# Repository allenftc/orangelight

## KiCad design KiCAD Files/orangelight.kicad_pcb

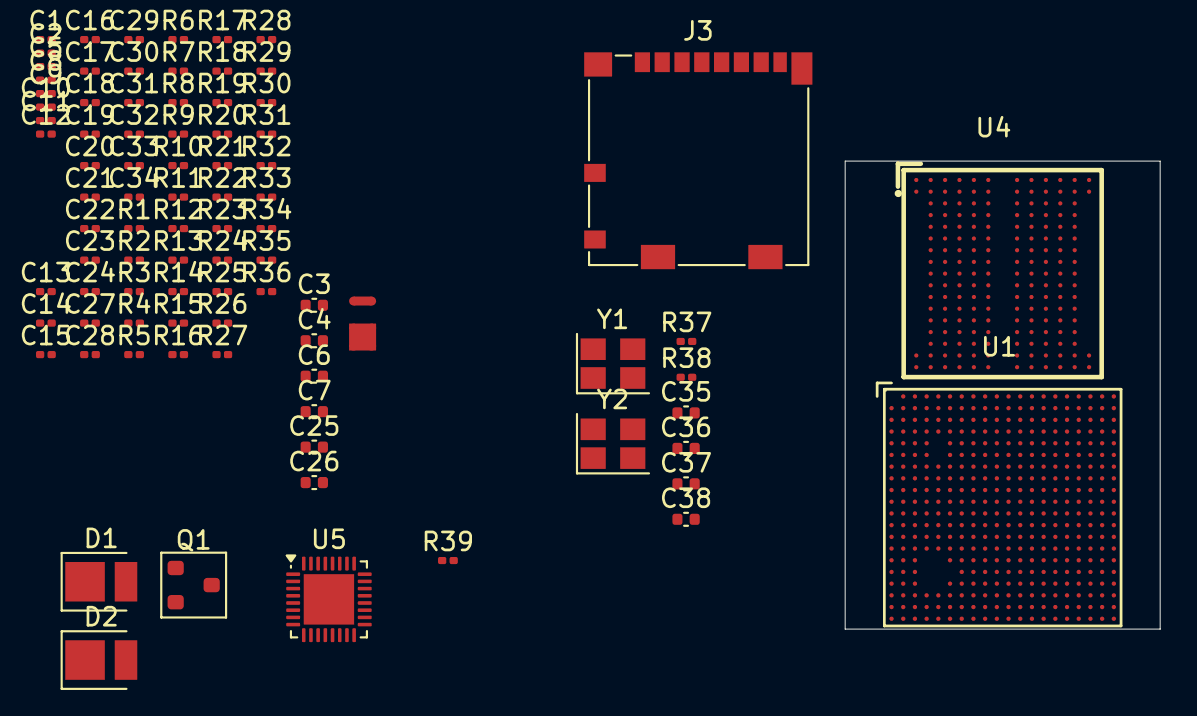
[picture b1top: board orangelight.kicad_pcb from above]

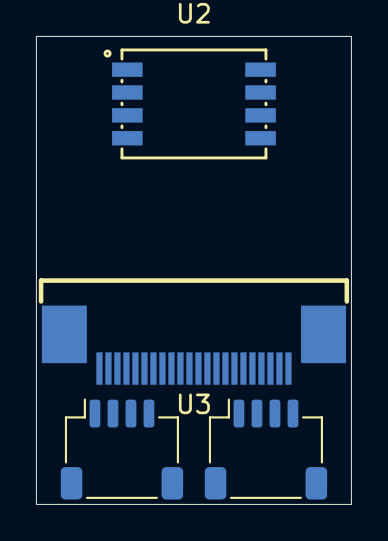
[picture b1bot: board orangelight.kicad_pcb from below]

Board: 2 copper layers, 17.5 x 26.0 mm, 92 parts (4 on the bottom side), 79 nets, no tracks yet.

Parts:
C1, C2, C5, C8, C9, C10, C11, C12, C13, C14, C15, C16, C17, C18, C19, C20, C21, C22, C23, C24, C27, C28, C29, C30, C31, C32, C33, C34: 100nF; C_0201_0603Metric
C3, C6, C25: 22uF; C_0402_1005Metric
C4, C7, C26: 4.7uF; C_0402_1005Metric
C35, C36, C37, C38: 15pF; C_0402_1005Metric
D1, D2: LED; LED_PLCC_2835
J1, J2: REV_JST_SMD; JST_SH_SM04B-SRSS-TB_1x04-1MP_P1.00mm_Horizontal
J3: Micro_SD_Card_Det2; microSD_HC_Molex_104031-0811
NT1: NetTie_2; NetTie-2_SMD_Pad0.5mm
NT2: NetTie_4; NetTie-4_SMD_Pad0.5mm
Q1: 2N7002; SOT-23
R1, R2, R36: 240R; R_0201_0603Metric
R3, R4, R5, R6, R7, R8, R9, R10, R11, R12, R13, R14, R15, R16, R17, R18, R19, R20, R21, R22, R23, R24, R25, R26, R27, R28, R29, R30, R31, R32, R33, R34, R35: 120R; R_0201_0603Metric
R37, R38: 1M; R_0201_0603Metric
R39: 200R; R_0201_0603Metric
U1: K230_Rewired; BGA-390_L13.0-W13.0-P0.65-TL_C9900054646
U2: ZDSD04GLGEAG; LGA-8_L8.0-W6.0-P1.27-TL-1
U3: HC-FPC-0_5-22P-CXH20; FPC-SMD_22P-P0.50_HC-FPC-0.5-22P-CXH20
U4: K4E8E324ED-EGCG; BGA-178_L11.5W11.0-P0.65-TL
U5: RT9992ZQW; Texas_RSN_WQFN-32-1EP_4x4mm_P0.4mm_EP2.8x2.8mm
Y1, Y2: 32.768KHz; Crystal_SMD_Abracon_ABM8AIG-4Pin_3.2x2.5mm

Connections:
+3V3: J1.3 (3.3V), J2.3 (3.3V), J3.4 (VDD), Q1.3 (D), U2.8 (VDD)
/RAM/DDR.CA0: R13.2, R14.1, U1.K20 (DDR_CA0_NC), U4.R2 (CA0)
/RAM/DDR.CA1: R15.2, R16.1, U1.L20 (DDR_CA1_NC), U4.P2 (CA1)
/RAM/DDR.CA2: R17.2, R18.1, U1.M20 (DDR_CA2_NA), U4.N2 (CA2)
/RAM/DDR.CA3: R19.2, R20.1, U1.L17 (DDR_CA3_NC), U4.N3 (CA3)
/RAM/DDR.CA4: R21.2, R22.1, U1.M19 (DDR_CA4_CAA0), U4.M3 (CA4)
/RAM/DDR.CA5: R23.2, R24.1, U1.L16 (DDR_CA5_CAA1), U4.F3 (CA5)
/RAM/DDR.CA6: R25.2, R26.1, U1.N19 (DDR_CA6_CAA2), U4.E3 (CA6)
/RAM/DDR.CA7: R27.2, R28.1, U1.N20 (DDR_CA7_CAA3), U4.E2 (CA7)
/RAM/DDR.CA8: R29.2, R30.1, U1.M18 (DDR_CA8_CAA4), U4.D2 (CA8)
/RAM/DDR.CA9: R31.2, R32.1, U1.P19 (DDR_CA9_CAA5), U4.C2 (CA9)
/RAM/DDR.CS: R3.2, R4.1, U4.L3 (CS_N)
/RAM/DDR.DM0: U1.D18 (DDR_DM0_DMIB0), U4.L8 (DM0)
/RAM/DDR.DM1: U1.P17 (DDR_DM1_DMIA1), U4.G8 (DM1)
/RAM/DDR.DM2: U1.C15 (DDR_DM2_DMIB1), U4.P8 (DM2)
/RAM/DDR.DM3: U1.V17 (DDR_DM3_DMIA0), U4.D8 (DM3)
/RAM/DDR.DQS_N0: U1.A18 (DDR_DQS0N_DQSB0N), U4.L11 (DQS0_c)
/RAM/DDR.DQS_N1: U1.V19 (DDR_DQS1N_DQSA1N), U4.G11 (DQS1_c)
/RAM/DDR.DQS_N2: U1.A15 (DDR_DQS2N_DQSB1N), U4.P11 (DQS2_c)
/RAM/DDR.DQS_N3: U1.Y17 (DDR_DQS3N_DQSA0N), U4.D11 (DQS3_c)
/RAM/DDR.DQS_P0: U1.B18 (DDR_DQS0P_DQSB0P), U4.L10 (DQS0_t)
/RAM/DDR.DQS_P1: U1.V20 (DDR_DQS1P_DQSA1P), U4.G10 (DQS1_t)
/RAM/DDR.DQS_P2: U1.B15 (DDR_DQS2P_DQSB1P), U4.P10 (DQS2_t)
/RAM/DDR.DQS_P3: U1.W17 (DDR_DQS3P_DQSA0P), U4.D10 (DQS3_t)
/RAM/DDR.ODT: R9.2, R10.1, U4.J8 (ODT(1))
/RAM/DDR.VREF_CA: C1.1, R33.2, R34.1, U4.H4 (VRef(CA))
/RAM/DDR.VREF_DQ: C2.1, R35.2, R36.1, U4.J11 (VRef(DQ))
/RAM/DDR_CK+: R7.2, R8.1, U4.J3 (CK_P)
/RAM/DDR_CK-: R5.2, R6.1, U4.J2 (CK_N)
/RAM/DDR_CKE: R11.2, R12.1, U4.K3 (CKE)
DDR_VDD1: C25.1, C26.1, C29.1, C30.1, C31.1, C32.1, C33.1, C34.1, NT1.2, U4.A3 (VDD1), U4.A4 (VDD1), U4.A5 (VDD1), U4.A6 (VDD1), U4.A10 (VDD1), U4.U3 (VDD1), U4.U4 (VDD1), U4.U5 (VDD1), U4.U6 (VDD1), U4.U10 (VDD1)
DDR_VDD2: NT2.2, U4.A8 (VDD2), U4.A9 (VDD2), U4.D4 (VDD2), U4.D5 (VDD2), U4.D6 (VDD2), U4.G5 (VDD2), U4.H5 (VDD2), U4.H6 (VDD2), U4.H12 (VDD2), U4.J5 (VDD2), U4.J6 (VDD2), U4.K5 (VDD2), U4.K6 (VDD2), U4.K12 (VDD2), U4.L5 (VDD2), U4.P4 (VDD2), U4.P5 (VDD2), U4.P6 (VDD2), U4.U8 (VDD2), U4.U9 (VDD2)
DDR_VDDCA: NT2.3, U4.F2 (VDDCA), U4.G2 (VDDCA), U4.H3 (VDDCA), U4.L2 (VDDCA), U4.M2 (VDDCA)
DDR_VDDQ: C3.1, C4.1, C5.1, C6.1, C7.1, C8.1, C9.1, C10.1, C11.1, C12.1, C13.1, C14.1, C15.1, C16.1, C17.1, C18.1, C19.1, C20.1, C21.1, C22.1, C23.1, C24.1, C27.1, C28.1, NT2.4, R3.1, R5.1, R7.1, R9.1, R11.1, R13.1, R15.1, R17.1, R19.1, R21.1, R23.1, R25.1, R27.1, R29.1, R31.1, R33.1, R35.1, U4.A11 (VDDQ), U4.C12 (VDDQ), U4.E8 (VDDQ), U4.E12 (VDDQ), U4.G12 (VDDQ), U4.H8 (VDDQ), U4.H9 (VDDQ), U4.H11 (VDDQ), U4.J9 (VDDQ), U4.J10 (VDDQ), U4.K8 (VDDQ), U4.K11 (VDDQ), U4.L12 (VDDQ), U4.N8 (VDDQ), U4.N12 (VDDQ), U4.R12 (VDDQ), U4.U11 (VDDQ)
GND: C1.2, C2.2, C3.2, C4.2, C5.2, C6.2, C7.2, C8.2, C9.2, C10.2, C11.2, C12.2, C13.2, C14.2, C15.2, C16.2, C17.2, C18.2, C19.2, C20.2, C21.2, C22.2, C23.2, C24.2, C25.2, C26.2, C27.2, C28.2, C29.2, C30.2, C31.2, C32.2, C33.2, C34.2, C35.2, C36.2, C37.2, C38.2, D1.1 (K), D2.1 (K), J1.4 (GND), J2.4 (GND), J3.6 (VSS), J3.11 (SHIELD), R1.2, R2.2, R4.2, R6.2, R8.2, R10.2, R12.2, R14.2, R16.2, R18.2, R20.2, R22.2, R24.2, R26.2, R28.2, R30.2, R32.2, R34.2, R36.2, R39.1, U2.4 (GND), U4.B2 (VSS), U4.B5 (VSS), U4.B6 (VSSQ), U4.B12 (VSSQ), U4.C3 (VSSCA), U4.C5 (VSS), U4.C6 (VSSQ), U4.D3 (VSSCA), U4.D12 (VSSQ), U4.E4 (VSS), U4.E5 (VSS), U4.E6 (VSSQ), U4.F4 (VSSCA), U4.F5 (VSS), U4.F6 (VSSQ), U4.F12 (VSSQ), U4.G3 (VSSCA), U4.G4 (VSSCA), U4.G6 (VSSQ), U4.G9 (VSSQ), U4.H2 (VSS), U4.H10 (VSSQ), U4.J4 (VSSCA), U4.J12 (VSS), U4.K2 (VSS), U4.K10 (VSSQ), U4.L6 (VSS), U4.L9 (VSSQ), U4.M4 (VSSCA), U4.M5 (VSSCA), U4.M6 (VSSQ), U4.M12 (VSSQ), U4.N4 (VSS), U4.N5 (VSS), U4.N6 (VSSQ), U4.P3 (VSSCA), U4.P12 (VSSQ), U4.R4 (VSS), U4.R5 (VSS), U4.R6 (VSSQ), U4.T2 (VSS), U4.T3 (VSS), U4.T4 (VSS), U4.T5 (VSS), U4.T6 (VSSQ), U4.T12 (VSSQ), Y1.2, Y1.4, Y2.2, Y2.4
unnamed: D1.2 (A), D2.2 (A), Q1.2 (S)
unnamed: J3.9 (DET_B), J3.10 (DET_A)
unnamed: C35.1, R37.2, Y1.3
unnamed: C36.1, R37.1, Y1.1
unnamed: C38.1, R38.2, Y2.3
unnamed: C37.1, R38.1, Y2.1
unnamed: U1.C17 (DDR_DQ0_DQB4), U4.P9 (DQ0)
unnamed: U1.D16 (DDR_DQ1_DQB1), U4.N9 (DQ1)
unnamed: U1.D17 (DDR_DQ2_DQB0), U4.N10 (DQ2)
unnamed: U1.C18 (DDR_DQ3_DQB5), U4.N11 (DQ3)
unnamed: U1.E18 (DDR_DQ4_DQB2), U4.M8 (DQ4)
unnamed: U1.E17 (DDR_DQ5_DQB3), U4.M9 (DQ5)
unnamed: U1.B19 (DDR_DQ6_DQB7), U4.M10 (DQ6)
unnamed: U1.C19 (DDR_DQ7_DQB6), U4.M11 (DQ7)
unnamed: U1.R18 (DDR_DQ8_DQA10), U4.F11 (DQ8)
unnamed: U1.P16 (DDR_DQ9_DQA14), U4.F10 (DQ9)
unnamed: U1.R17 (DDR_DQ10_DQA8), U4.F9 (DQ10)
unnamed: U1.W19 (DDR_DQ11_DQA12), U4.F8 (DQ11)
unnamed: U1.T18 (DDR_DQ12_DQA9), U4.E11 (DQ12)
unnamed: U1.U20 (DDR_DQ13_DQA11), U4.E10 (DQ13)
unnamed: U1.U18 (DDR_DQ14_DQA13), U4.E9 (DQ14)
unnamed: U1.T17 (DDR_DQ15_DQA15), U4.D9 (DQ15)
unnamed: U1.C14 (DDR_DQ16_DQB11), U4.T8 (DQ16)
unnamed: U1.B14 (DDR_DQ17_DQB10), U4.T9 (DQ17)
unnamed: U1.C16 (DDR_DQ18_DQB13), U4.T10 (DQ18)
unnamed: U1.A17 (DDR_DQ19_DQB14), U4.T11 (DQ19)
unnamed: U1.D14 (DDR_DQ20_DQB8), U4.R8 (DQ20)
unnamed: U1.A14 (DDR_DQ21_DQB9), U4.R9 (DQ21)
unnamed: U1.B17 (DDR_DQ22_DQB12), U4.R10 (DQ22)
unnamed: U1.B16 (DDR_DQ23_DQB15), U4.R11 (DQ23)
unnamed: U1.W18 (DDR_DQ24_DQA4), U4.C11 (DQ24)
unnamed: U1.V18 (DDR_DQ25_DQA5), U4.C10 (DQ25)
unnamed: U1.V16 (DDR_DQ26_DQA2), U4.C9 (DQ26)
unnamed: U1.Y16 (DDR_DQ27_DQA3), U4.C8 (DQ27)
unnamed: U1.Y18 (DDR_DQ28_DQA6), U4.B11 (DQ28)
unnamed: U1.U17 (DDR_DQ29_DQA7), U4.B10 (DQ29)
unnamed: U1.T16 (DDR_DQ30_DQA1), U4.B9 (DQ30)
unnamed: U1.U16 (DDR_DQ31_DQA0), U4.B8 (DQ31)
unnamed: U1.A16 (VSS), U1.L15 (VSS)
unnamed: U1.C13 (VSS), U1.N12 (VSS)
unnamed: U1.E12 (VSS), U1.R12 (VSS)
unnamed: U1.E14 (VSS), U1.R14 (VSS)
unnamed: U1.E16 (VSS), U1.R16 (VSS)
unnamed: R2.1, U4.B3 (ZQ)

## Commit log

2025-07-09 a lot of stuff happened
2025-07-09 reorganziation
2025-07-10 added ram and flash
2025-07-14 more peripherals
2025-07-15 schematic is pretty much done
